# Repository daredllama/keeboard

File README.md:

# Keeboard

A custom 75%-layout mechanical keyboard, with per-key backlighting, a rotary encoder, a OLED status display, and RMK (Rust) firmware on an RP2040 (Raspberry Pi Pico).

---

## Features

- **79-keys** (78 keys + integrated rotary encoder pushbutton)
- **Per-key backlighting** — SK6812 Mini LEDs, one per switch
- **Rotary encoder** (EC11) — rotation bound to volume, click bound to OLED toggle
- **128×64 I2C OLED** - status display 
- **RMK firmware** (Rust) running on RP2040
- **Sandwich mount** case, plate-mount stabilizers, Cherry MX-compatible switches

---

## Hardware

| Component | Spec |
|---|---|
| MCU | Raspberry Pi Pico (RP2040) |
| Switches | Cherry MX-compatible |
| LEDs | SK6812 Mini, ~79x, per-key |
| Diodes | 1N4148WS (SOD-323) |
| Decoupling caps | 100nF ceramic, 0402 |
| Encoder | EC11 |
| Display | 128×64 I2C OLED (0.96") |
| Stabilizers | Cherry-style plate-mount — 2u (Backspace, Enter, LShift), 6.25u (Spacebar) |

## Plate / Case

- Case screws: M3

## Pin Mapping (RP2040 / Pico)

| Function | GPIO |
|---|---|
| Columns (col0–col14) | GPIO0, 9, 7, 12, 13, 3, 14, 20, 17, 6, 16, 5, 4, 2, 21 |
| Rows (row0–row5) | GPIO15, 11, 10, 8, 1, 22 |
| Encoder A / B | GPIO18 / GPIO19 |
| LED data | GPIO26 |
| OLED SDA / SCL | GPIO27 / GPIO28 |

## Firmware

**Flashing:**
1. Hold the Pico's BOOTSEL button while plugging it in via USB
2. `cargo run --release`
   (uses `elf2uf2-rs` by default — install once with `cargo install elf2uf2-rs`)

**Keymap:** defined in `keyboard.toml` under `[layout].keymap`. 3 layers:
- **Layer 0** — base QWERTY layout matching the F75 layout
- **Layer 1** — Fn layer, RGB controls (mode/brightness on arrow keys)
- **Layer 2** — reserved

## PCB / Assembly Notes

- LEDs are intended to be **reverse-mounted** (bottom side, shining through a PCB cutout) — assembled and soldered by hand, **not** included in the JLCPCB assembly BOM/CPL

## Reflection

For this build, I really challenged myself with tedious ahh work. Even though that making this board was quite tedious, it was a good learning experience,
espcially since this is my first-ever keyboard. I wanted to add a OLED screen so that I could have cool animations or somthing moving on the keyboard while 
I typed. I learned many things form this project, such as how tedious it is to put per-key LEDS for every key. That might have been a mistake. But, I also
learned how to edit/make footprints.

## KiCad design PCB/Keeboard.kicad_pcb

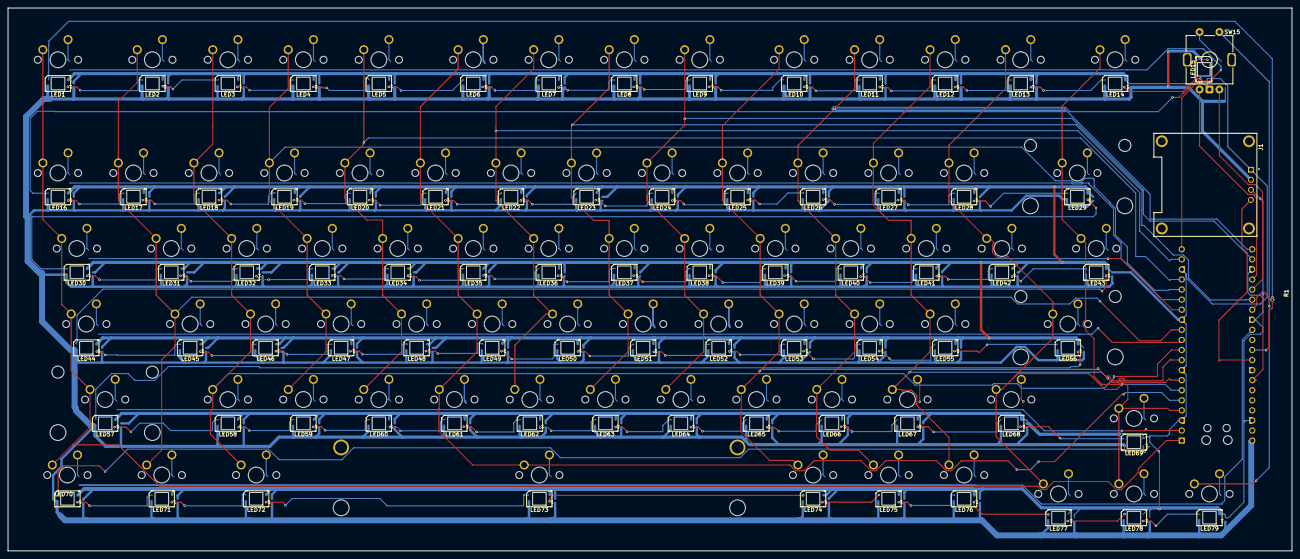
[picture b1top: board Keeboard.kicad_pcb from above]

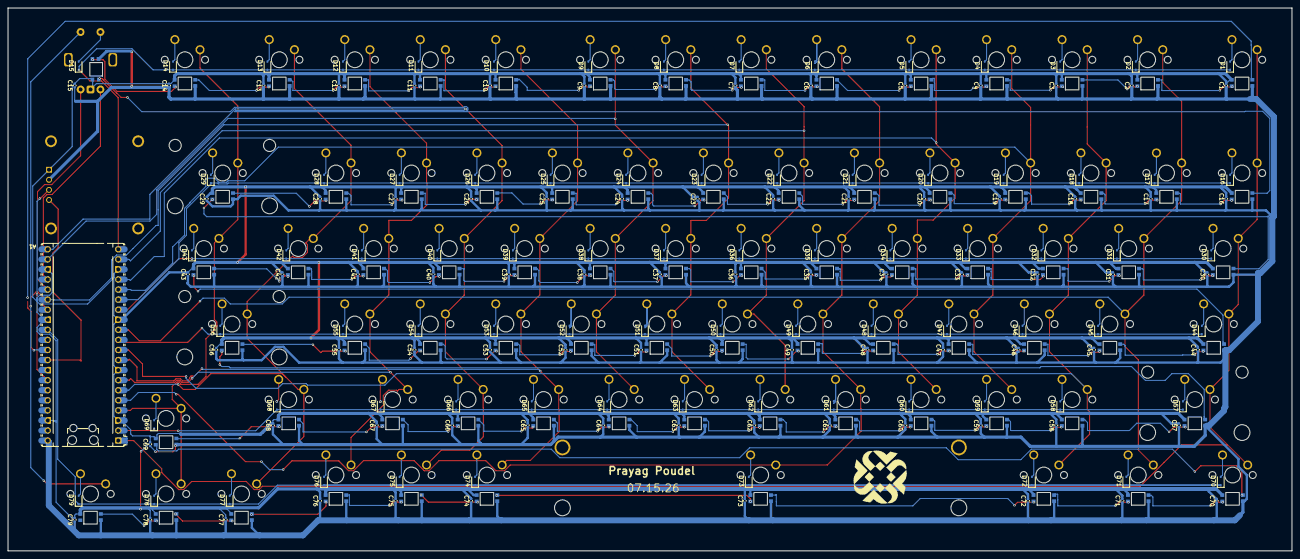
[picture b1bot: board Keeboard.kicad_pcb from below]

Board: 2 copper layers, 323.9 x 136.9 mm, 323 parts (159 on the bottom side), 186 nets.

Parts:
A1: RaspberryPi_Pico; RaspberryPi_Pico_Common_Unspecified
C1, C2, C3, C4, C5, C6, C7, C8, C9, C10, C11, C12, C13, C14, C15, C16, C17, C18, C19, C20, C21, C22, C23, C24, C25, C26, C27, C28, C29, C30, C31, C32, C33, C34, C35, C36, C37, C38, C39, C40, C41, C42, C43, C44, C45, C46, C47, C48, C49, C50, C51, C52, C53, C54, C55, C56, C57, C58, C59, C60, C61, C62, C63, C64, C65, C66, C67, C68, C69, C70, C71, C72, C73, C74, C75, C76, C77, C78, C79: 100nF; C_0402_1005Metric
D1, D2, D3, D4, D5, D6, D7, D8, D9, D10, D11, D12, D13, D14, D15, D16, D17, D18, D19, D20, D21, D22, D23, D24, D25, D26, D27, D28, D29, D30, D31, D32, D33, D34, D35, D36, D37, D38, D39, D40, D41, D42, D43, D44, D45, D46, D47, D48, D49, D50, D51, D52, D53, D54, D55, D56, D57, D58, D59, D60, D61, D62, D63, D64, D65, D66, D67, D68, D69, D70, D71, D72, D73, D74, D75, D76, D77, D78, D79: Diode; D_SOD-323
J1: OLED; MODULE_DM-OLED096-636
LED1, LED2, LED3, LED4, LED5, LED6, LED7, LED8, LED9, LED10, LED11, LED12, LED13, LED14, LED15, LED16, LED17, LED18, LED19, LED20, LED21, LED22, LED23, LED24, LED25, LED26, LED27, LED28, LED29, LED30, LED31, LED32, LED33, LED34, LED35, LED36, LED37, LED38, LED39, LED40, LED41, LED42, LED43, LED44, LED45, LED46, LED47, LED48, LED49, LED50, LED51, LED52, LED53, LED54, LED55, LED56, LED57, LED58, LED59, LED60, LED61, LED62, LED63, LED64, LED65, LED66, LED67, LED68, LED69, LED70, LED71, LED72, LED73, LED74, LED75, LED76, LED77, LED78, LED79: SK6812MINI; LED_SK6812MINI_PLCC4_3.5x3.5mm_P1.75mm_1
R1: 500; R_0402_1005Metric
ST29: MX_stab; STAB_MX_2u
ST56, ST57: MX_stab; STAB_MX_2.25u
ST73: MX_stab; STAB_MX_P_6.25u
SW1, SW2, SW3, SW4, SW5, SW6, SW7, SW8, SW9, SW10, SW11, SW12, SW13, SW14, SW16, SW17, SW18, SW19, SW20, SW21, SW22, SW23, SW24, SW25, SW26, SW27, SW28, SW29, SW31, SW32, SW33, SW34, SW35, SW36, SW37, SW38, SW39, SW40, SW41, SW42, SW45, SW46, SW47, SW48, SW49, SW50, SW51, SW52, SW53, SW54, SW55, SW56, SW57, SW58, SW59, SW60, SW61, SW62, SW63, SW64, SW65, SW66, SW67, SW69, SW73, SW74, SW75, SW76, SW77, SW78, SW79: SW_MX_1u
SW15: Rotary; ROT_Alps_EC11E-Switch
SW30, SW43: SW_MX_1.5u
SW44, SW68: SW_MX_1.75u
SW70, SW71, SW72: SW_MX_1.25u

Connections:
+5V: A1.40 (VBUS), C1.1, C2.1, C3.1, C4.1, C5.1, C6.1, C7.1, C8.1, C9.1, C10.1, C11.1, C12.1, C13.1, C14.1, C15.1, C16.1, C17.1, C18.1, C19.1, C20.1, C21.1, C22.1, C23.1, C24.1, C25.1, C26.1, C27.1, C28.1, C29.1, C30.1, C31.1, C32.1, C33.1, C34.1, C35.1, C36.1, C37.1, C38.1, C39.1, C40.1, C41.1, C42.1, C43.1, C44.1, C45.1, C46.1, C47.1, C48.1, C49.1, C50.1, C51.1, C52.1, C53.1, C54.1, C55.1, C56.1, C57.1, C58.1, C59.1, C60.1, C61.1, C62.1, C63.1, C64.1, C65.1, C66.1, C67.1, C68.1, C69.1, C70.1, C71.1, C72.1, C73.1, C74.1, C75.1, C76.1, C77.1, C78.1, C79.1, J1.2, LED1.4 (VDD), LED2.4 (VDD), LED3.4 (VDD), LED4.4 (VDD), LED5.4 (VDD), LED6.4 (VDD), LED7.4 (VDD), LED8.4 (VDD), LED9.4 (VDD), LED10.4 (VDD), LED11.4 (VDD), LED12.4 (VDD), LED13.4 (VDD), LED14.4 (VDD), LED15.4 (VDD), LED16.4 (VDD), LED17.4 (VDD), LED18.4 (VDD), LED19.4 (VDD), LED20.4 (VDD), LED21.4 (VDD), LED22.4 (VDD), LED23.4 (VDD), LED24.4 (VDD), LED25.4 (VDD), LED26.4 (VDD), LED27.4 (VDD), LED28.4 (VDD), LED29.4 (VDD), LED30.4 (VDD), LED31.4 (VDD), LED32.4 (VDD), LED33.4 (VDD), LED34.4 (VDD), LED35.4 (VDD), LED36.4 (VDD), LED37.4 (VDD), LED38.4 (VDD), LED39.4 (VDD), LED40.4 (VDD), LED41.4 (VDD), LED42.4 (VDD), LED43.4 (VDD), LED44.4 (VDD), LED45.4 (VDD), LED46.4 (VDD), LED47.4 (VDD), LED48.4 (VDD), LED49.4 (VDD), LED50.4 (VDD), LED51.4 (VDD), LED52.4 (VDD), LED53.4 (VDD), LED54.4 (VDD), LED55.4 (VDD), LED56.4 (VDD), LED57.4 (VDD), LED58.4 (VDD), LED59.4 (VDD), LED60.4 (VDD), LED61.4 (VDD), LED62.4 (VDD), LED63.4 (VDD), LED64.4 (VDD), LED65.4 (VDD), LED66.4 (VDD), LED67.4 (VDD), LED68.4 (VDD), LED69.4 (VDD), LED70.4 (VDD), LED71.4 (VDD), LED72.4 (VDD), LED73.4 (VDD), LED74.4 (VDD), LED75.4 (VDD), LED76.4 (VDD), LED77.4 (VDD), LED78.4 (VDD), LED79.4 (VDD)
GND: A1.3 (GND), A1.8 (GND), A1.13 (GND), A1.18 (GND), A1.23 (GND), A1.28 (GND), A1.38 (GND), C1.2, C2.2, C3.2, C4.2, C5.2, C6.2, C7.2, C8.2, C9.2, C10.2, C11.2, C12.2, C13.2, C14.2, C15.2, C16.2, C17.2, C18.2, C19.2, C20.2, C21.2, C22.2, C23.2, C24.2, C25.2, C26.2, C27.2, C28.2, C29.2, C30.2, C31.2, C32.2, C33.2, C34.2, C35.2, C36.2, C37.2, C38.2, C39.2, C40.2, C41.2, C42.2, C43.2, C44.2, C45.2, C46.2, C47.2, C48.2, C49.2, C50.2, C51.2, C52.2, C53.2, C54.2, C55.2, C56.2, C57.2, C58.2, C59.2, C60.2, C61.2, C62.2, C63.2, C64.2, C65.2, C66.2, C67.2, C68.2, C69.2, C70.2, C71.2, C72.2, C73.2, C74.2, C75.2, C76.2, C77.2, C78.2, C79.2, J1.1, LED1.2 (VSS), LED2.2 (VSS), LED3.2 (VSS), LED4.2 (VSS), LED5.2 (VSS), LED6.2 (VSS), LED7.2 (VSS), LED8.2 (VSS), LED9.2 (VSS), LED10.2 (VSS), LED11.2 (VSS), LED12.2 (VSS), LED13.2 (VSS), LED14.2 (VSS), LED15.2 (VSS), LED16.2 (VSS), LED17.2 (VSS), LED18.2 (VSS), LED19.2 (VSS), LED20.2 (VSS), LED21.2 (VSS), LED22.2 (VSS), LED23.2 (VSS), LED24.2 (VSS), LED25.2 (VSS), LED26.2 (VSS), LED27.2 (VSS), LED28.2 (VSS), LED29.2 (VSS), LED30.2 (VSS), LED31.2 (VSS), LED32.2 (VSS), LED33.2 (VSS), LED34.2 (VSS), LED35.2 (VSS), LED36.2 (VSS), LED37.2 (VSS), LED38.2 (VSS), LED39.2 (VSS), LED40.2 (VSS), LED41.2 (VSS), LED42.2 (VSS), LED43.2 (VSS), LED44.2 (VSS), LED45.2 (VSS), LED46.2 (VSS), LED47.2 (VSS), LED48.2 (VSS), LED49.2 (VSS), LED50.2 (VSS), LED51.2 (VSS), LED52.2 (VSS), LED53.2 (VSS), LED54.2 (VSS), LED55.2 (VSS), LED56.2 (VSS), LED57.2 (VSS), LED58.2 (VSS), LED59.2 (VSS), LED60.2 (VSS), LED61.2 (VSS), LED62.2 (VSS), LED63.2 (VSS), LED64.2 (VSS), LED65.2 (VSS), LED66.2 (VSS), LED67.2 (VSS), LED68.2 (VSS), LED69.2 (VSS), LED70.2 (VSS), LED71.2 (VSS), LED72.2 (VSS), LED73.2 (VSS), LED74.2 (VSS), LED75.2 (VSS), LED76.2 (VSS), LED77.2 (VSS), LED78.2 (VSS), LED79.2 (VSS), SW15.C
LED: A1.31 (GPIO26_ADC0), R1.2
unnamed: D1.2 (A), SW1.2
unnamed: D2.2 (A), SW2.2
unnamed: D3.2 (A), SW3.2
unnamed: D4.2 (A), SW4.2
unnamed: D5.2 (A), SW5.2
unnamed: D6.2 (A), SW6.2
unnamed: D7.2 (A), SW7.2
unnamed: D8.2 (A), SW8.2
unnamed: D9.2 (A), SW9.2
unnamed: D10.2 (A), SW10.2
unnamed: D11.2 (A), SW11.2
unnamed: D12.2 (A), SW12.2
unnamed: D13.2 (A), SW13.2
unnamed: D14.2 (A), SW14.2
unnamed: D16.2 (A), SW16.2
unnamed: D17.2 (A), SW17.2
unnamed: D18.2 (A), SW18.2
unnamed: D19.2 (A), SW19.2
unnamed: D20.2 (A), SW20.2
unnamed: D21.2 (A), SW21.2
unnamed: D22.2 (A), SW22.2
unnamed: D23.2 (A), SW23.2
unnamed: D24.2 (A), SW24.2
unnamed: D25.2 (A), SW25.2
unnamed: D26.2 (A), SW26.2
unnamed: D27.2 (A), SW27.2
unnamed: D28.2 (A), SW28.2
unnamed: D29.2 (A), SW29.2
unnamed: D30.2 (A), SW30.2
unnamed: D31.2 (A), SW31.2
unnamed: D32.2 (A), SW32.2
unnamed: D33.2 (A), SW33.2
unnamed: D34.2 (A), SW34.2
unnamed: D35.2 (A), SW35.2
unnamed: D36.2 (A), SW36.2
unnamed: D37.2 (A), SW37.2
unnamed: D38.2 (A), SW38.2
unnamed: D39.2 (A), SW39.2
unnamed: D40.2 (A), SW40.2
unnamed: D41.2 (A), SW41.2
unnamed: D42.2 (A), SW42.2
unnamed: D43.2 (A), SW43.2
unnamed: D44.2 (A), SW44.2
unnamed: D45.2 (A), SW45.2
unnamed: D46.2 (A), SW46.2
unnamed: D47.2 (A), SW47.2
unnamed: D48.2 (A), SW48.2
unnamed: D49.2 (A), SW49.2
unnamed: D50.2 (A), SW50.2
unnamed: D51.2 (A), SW51.2
unnamed: D52.2 (A), SW52.2
unnamed: D53.2 (A), SW53.2
unnamed: D54.2 (A), SW54.2
unnamed: D55.2 (A), SW55.2
unnamed: D56.2 (A), SW56.2
unnamed: D57.2 (A), SW57.2
unnamed: D58.2 (A), SW58.2
unnamed: D59.2 (A), SW59.2
unnamed: D60.2 (A), SW60.2
unnamed: D61.2 (A), SW61.2
unnamed: D62.2 (A), SW62.2
unnamed: D63.2 (A), SW63.2
unnamed: D64.2 (A), SW64.2
unnamed: D65.2 (A), SW65.2
unnamed: D66.2 (A), SW66.2
unnamed: D67.2 (A), SW67.2
unnamed: D68.2 (A), SW68.2
unnamed: D69.2 (A), SW69.2
unnamed: D70.2 (A), SW70.2
unnamed: D71.2 (A), SW71.2
unnamed: D72.2 (A), SW72.2
unnamed: D73.2 (A), SW73.2
unnamed: D74.2 (A), SW74.2
unnamed: D75.2 (A), SW75.2
unnamed: D76.2 (A), SW76.2
unnamed: D77.2 (A), SW77.2
unnamed: D78.2 (A), SW78.2
unnamed: D79.2 (A), SW79.2
unnamed: LED1.3 (DIN), R1.1
unnamed: LED1.1 (DOUT), LED2.3 (DIN)
unnamed: LED2.1 (DOUT), LED3.3 (DIN)
unnamed: LED3.1 (DOUT), LED4.3 (DIN)
unnamed: LED4.1 (DOUT), LED5.3 (DIN)
unnamed: LED5.1 (DOUT), LED6.3 (DIN)
unnamed: LED6.1 (DOUT), LED7.3 (DIN)
unnamed: LED7.1 (DOUT), LED8.3 (DIN)
unnamed: LED8.1 (DOUT), LED9.3 (DIN)
unnamed: LED9.1 (DOUT), LED10.3 (DIN)
unnamed: LED10.1 (DOUT), LED11.3 (DIN)
unnamed: LED11.1 (DOUT), LED12.3 (DIN)
unnamed: LED12.1 (DOUT), LED13.3 (DIN)
unnamed: LED13.1 (DOUT), LED14.3 (DIN)
unnamed: LED14.1 (DOUT), LED15.3 (DIN)
unnamed: LED15.1 (DOUT), LED16.3 (DIN)
unnamed: LED16.1 (DOUT), LED17.3 (DIN)
unnamed: LED17.1 (DOUT), LED18.3 (DIN)
unnamed: LED18.1 (DOUT), LED19.3 (DIN)
unnamed: LED19.1 (DOUT), LED20.3 (DIN)
unnamed: LED20.1 (DOUT), LED21.3 (DIN)
unnamed: LED21.1 (DOUT), LED22.3 (DIN)
unnamed: LED22.1 (DOUT), LED23.3 (DIN)
unnamed: LED23.1 (DOUT), LED24.3 (DIN)
unnamed: LED24.1 (DOUT), LED25.3 (DIN)
unnamed: LED25.1 (DOUT), LED26.3 (DIN)
unnamed: LED26.1 (DOUT), LED27.3 (DIN)
unnamed: LED27.1 (DOUT), LED28.3 (DIN)
unnamed: LED28.1 (DOUT), LED29.3 (DIN)
unnamed: LED29.1 (DOUT), LED30.3 (DIN)
unnamed: LED30.1 (DOUT), LED31.3 (DIN)
unnamed: LED31.1 (DOUT), LED32.3 (DIN)
unnamed: LED32.1 (DOUT), LED33.3 (DIN)
unnamed: LED33.1 (DOUT), LED34.3 (DIN)
unnamed: LED34.1 (DOUT), LED35.3 (DIN)
unnamed: LED35.1 (DOUT), LED36.3 (DIN)
unnamed: LED36.1 (DOUT), LED37.3 (DIN)
unnamed: LED37.1 (DOUT), LED38.3 (DIN)
unnamed: LED38.1 (DOUT), LED39.3 (DIN)
unnamed: LED39.1 (DOUT), LED40.3 (DIN)
unnamed: LED40.1 (DOUT), LED41.3 (DIN)
unnamed: LED41.1 (DOUT), LED42.3 (DIN)
unnamed: LED42.1 (DOUT), LED43.3 (DIN)
unnamed: LED43.1 (DOUT), LED44.3 (DIN)
unnamed: LED44.1 (DOUT), LED45.3 (DIN)
unnamed: LED45.1 (DOUT), LED46.3 (DIN)
unnamed: LED46.1 (DOUT), LED47.3 (DIN)
unnamed: LED47.1 (DOUT), LED48.3 (DIN)
unnamed: LED48.1 (DOUT), LED49.3 (DIN)
unnamed: LED49.1 (DOUT), LED50.3 (DIN)
unnamed: LED50.1 (DOUT), LED51.3 (DIN)
unnamed: LED51.1 (DOUT), LED52.3 (DIN)
unnamed: LED52.1 (DOUT), LED53.3 (DIN)
unnamed: LED53.1 (DOUT), LED54.3 (DIN)
unnamed: LED54.1 (DOUT), LED55.3 (DIN)
unnamed: LED55.1 (DOUT), LED56.3 (DIN)
unnamed: LED56.1 (DOUT), LED57.3 (DIN)
unnamed: LED57.1 (DOUT), LED58.3 (DIN)
unnamed: LED58.1 (DOUT), LED59.3 (DIN)
unnamed: LED59.1 (DOUT), LED60.3 (DIN)
unnamed: LED60.1 (DOUT), LED61.3 (DIN)
unnamed: LED61.1 (DOUT), LED62.3 (DIN)
unnamed: LED62.1 (DOUT), LED63.3 (DIN)
unnamed: LED63.1 (DOUT), LED64.3 (DIN)
unnamed: LED64.1 (DOUT), LED65.3 (DIN)
unnamed: LED65.1 (DOUT), LED66.3 (DIN)
unnamed: LED66.1 (DOUT), LED67.3 (DIN)
unnamed: LED67.1 (DOUT), LED68.3 (DIN)
unnamed: LED68.1 (DOUT), LED69.3 (DIN)
unnamed: LED69.1 (DOUT), LED70.3 (DIN)
unnamed: LED70.1 (DOUT), LED71.3 (DIN)
unnamed: LED71.1 (DOUT), LED72.3 (DIN)
unnamed: LED72.1 (DOUT), LED73.3 (DIN)
unnamed: LED73.1 (DOUT), LED74.3 (DIN)
unnamed: LED74.1 (DOUT), LED75.3 (DIN)
unnamed: LED75.1 (DOUT), LED76.3 (DIN)
unnamed: LED76.1 (DOUT), LED77.3 (DIN)
unnamed: LED77.1 (DOUT), LED78.3 (DIN)
unnamed: LED78.1 (DOUT), LED79.3 (DIN)
RotA: A1.24 (GPIO18), SW15.A
RotB: A1.25 (GPIO19), SW15.B
RotS1: A1.27 (GPIO21), SW15.S1, SW79.1
RotS2: D15.2 (A), SW15.S2
SCL: A1.34 (GPIO28_ADC2), J1.3
SDA: A1.32 (GPIO27_ADC1), J1.4
col0: A1.1 (GPIO0), SW1.1, SW16.1, SW30.1, SW44.1, SW57.1, SW70.1
col1: A1.12 (GPIO9), SW2.1, SW17.1, SW31.1, SW45.1, SW71.1
col2: A1.10 (GPIO7), SW3.1, SW18.1, SW32.1, SW46.1, SW58.1, SW72.1
col3: A1.16 (GPIO12), SW4.1, SW19.1, SW33.1, SW47.1, SW59.1
col4: A1.17 (GPIO13), SW5.1, SW20.1, SW34.1, SW48.1, SW60.1
col5: A1.5 (GPIO3), SW6.1, SW21.1, SW35.1, SW49.1, SW61.1, SW73.1
col6: A1.19 (GPIO14), SW7.1, SW22.1, SW36.1, SW50.1, SW62.1
col7: A1.26 (GPIO20), SW8.1, SW23.1, SW37.1, SW51.1, SW63.1
col8: A1.22 (GPIO17), SW9.1, SW24.1, SW38.1, SW52.1, SW64.1
col9: A1.9 (GPIO6), SW10.1, SW25.1, SW39.1, SW53.1, SW65.1, SW74.1
col10: A1.21 (GPIO16), SW11.1, SW26.1, SW40.1, SW54.1, SW66.1, SW75.1
col11: A1.7 (GPIO5), SW12.1, SW27.1, SW41.1, SW55.1, SW67.1, SW76.1
col12: A1.6 (GPIO4), SW13.1, SW28.1, SW42.1, SW56.1, SW68.1, SW77.1
col13: A1.4 (GPIO2), SW14.1, SW29.1, SW43.1, SW69.1, SW78.1
row0: A1.20 (GPIO15), D1.1 (K), D2.1 (K), D3.1 (K), D4.1 (K), D5.1 (K), D6.1 (K), D7.1 (K), D8.1 (K), D9.1 (K), D10.1 (K), D11.1 (K), D12.1 (K), D13.1 (K), D14.1 (K), D15.1 (K)
row1: A1.15 (GPIO11), D16.1 (K), D17.1 (K), D18.1 (K), D19.1 (K), D20.1 (K), D21.1 (K), D22.1 (K), D23.1 (K), D24.1 (K), D25.1 (K), D26.1 (K), D27.1 (K), D28.1 (K), D29.1 (K)
row2: A1.14 (GPIO10), D30.1 (K), D31.1 (K), D32.1 (K), D33.1 (K), D34.1 (K), D35.1 (K), D36.1 (K), D37.1 (K), D38.1 (K), D39.1 (K), D40.1 (K), D41.1 (K), D42.1 (K), D43.1 (K)
row3: A1.11 (GPIO8), D44.1 (K), D45.1 (K), D46.1 (K), D47.1 (K), D48.1 (K), D49.1 (K), D50.1 (K), D51.1 (K), D52.1 (K), D53.1 (K), D54.1 (K), D55.1 (K), D56.1 (K)
row4: A1.2 (GPIO1), D57.1 (K), D58.1 (K), D59.1 (K), D60.1 (K), D61.1 (K), D62.1 (K), D63.1 (K), D64.1 (K), D65.1 (K), D66.1 (K), D67.1 (K), D68.1 (K), D69.1 (K)
row5: A1.29 (GPIO22), D70.1 (K), D71.1 (K), D72.1 (K), D73.1 (K), D74.1 (K), D75.1 (K), D76.1 (K), D77.1 (K), D78.1 (K), D79.1 (K)

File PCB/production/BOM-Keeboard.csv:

Comment,Designator,Footprint,LCSC,Quantity
100nF,"C1,C10,C11,C12,C13,C14,C15,C16,C17,C18,C19,C2,C20,C21,C22,C23,C24,C25,C26,C27,C28,C29,C3,C30,C31,C32,C33,C34,C35,C36,C37,C38,C39,C4,C40,C41,C42,C43,C44,C45,C46,C47,C48,C49,C5,C50,C51,C52,C53,C54,C55,C56,C57,C58,C59,C6,C60,C61,C62,C63,C64,C65,C66,C67,C68,C69,C7,C70,C71,C72,C73,C74,C75,C76,C77,C78,C79,C8,C9",C_0402_1005Metric,C1525,79
500,R1,R_0402_1005Metric,C6460545,1
Diode,"D1,D10,D11,D12,D13,D14,D15,D16,D17,D18,D19,D2,D20,D21,D22,D23,D24,D25,D26,D27,D28,D29,D3,D30,D31,D32,D33,D34,D35,D36,D37,D38,D39,D4,D40,D41,D42,D43,D44,D45,D46,D47,D48,D49,D5,D50,D51,D52,D53,D54,D55,D56,D57,D58,D59,D6,D60,D61,D62,D63,D64,D65,D66,D67,D68,D69,D7,D70,D71,D72,D73,D74,D75,D76,D77,D78,D79,D8,D9",D_SOD-323,C2128,79
SK6812MINI,"LED1,LED10,LED11,LED12,LED13,LED14,LED15,LED16,LED17,LED18,LED19,LED2,LED20,LED21,LED22,LED23,LED24,LED25,LED26,LED27,LED28,LED29,LED3,LED30,LED31,LED32,LED33,LED34,LED35,LED36,LED37,LED38,LED39,LED4,LED40,LED41,LED42,LED43,LED44,LED45,LED46,LED47,LED48,LED49,LED5,LED50,LED51,LED52,LED53,LED54,LED55,LED56,LED57,LED58,LED59,LED6,LED60,LED61,LED62,LED63,LED64,LED65,LED66,LED67,LED68,LED69,LED7,LED70,LED71,LED72,LED73,LED74,LED75,LED76,LED77,LED78,LED79,LED8,LED9",LED_SK6812MINI_PLCC4_3.5x3.5mm_Correct,C5149201,79
